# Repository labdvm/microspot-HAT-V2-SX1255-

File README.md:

# microspot-HAT-V2
SX1255 TMO microspot-HAT with integrated ceramic antennas
# V1 was deleted !

# Corrections of ceramic antenna dimensions from 16mm to 14mm.
# Added IPX connectors for external antennas.

Z32IT

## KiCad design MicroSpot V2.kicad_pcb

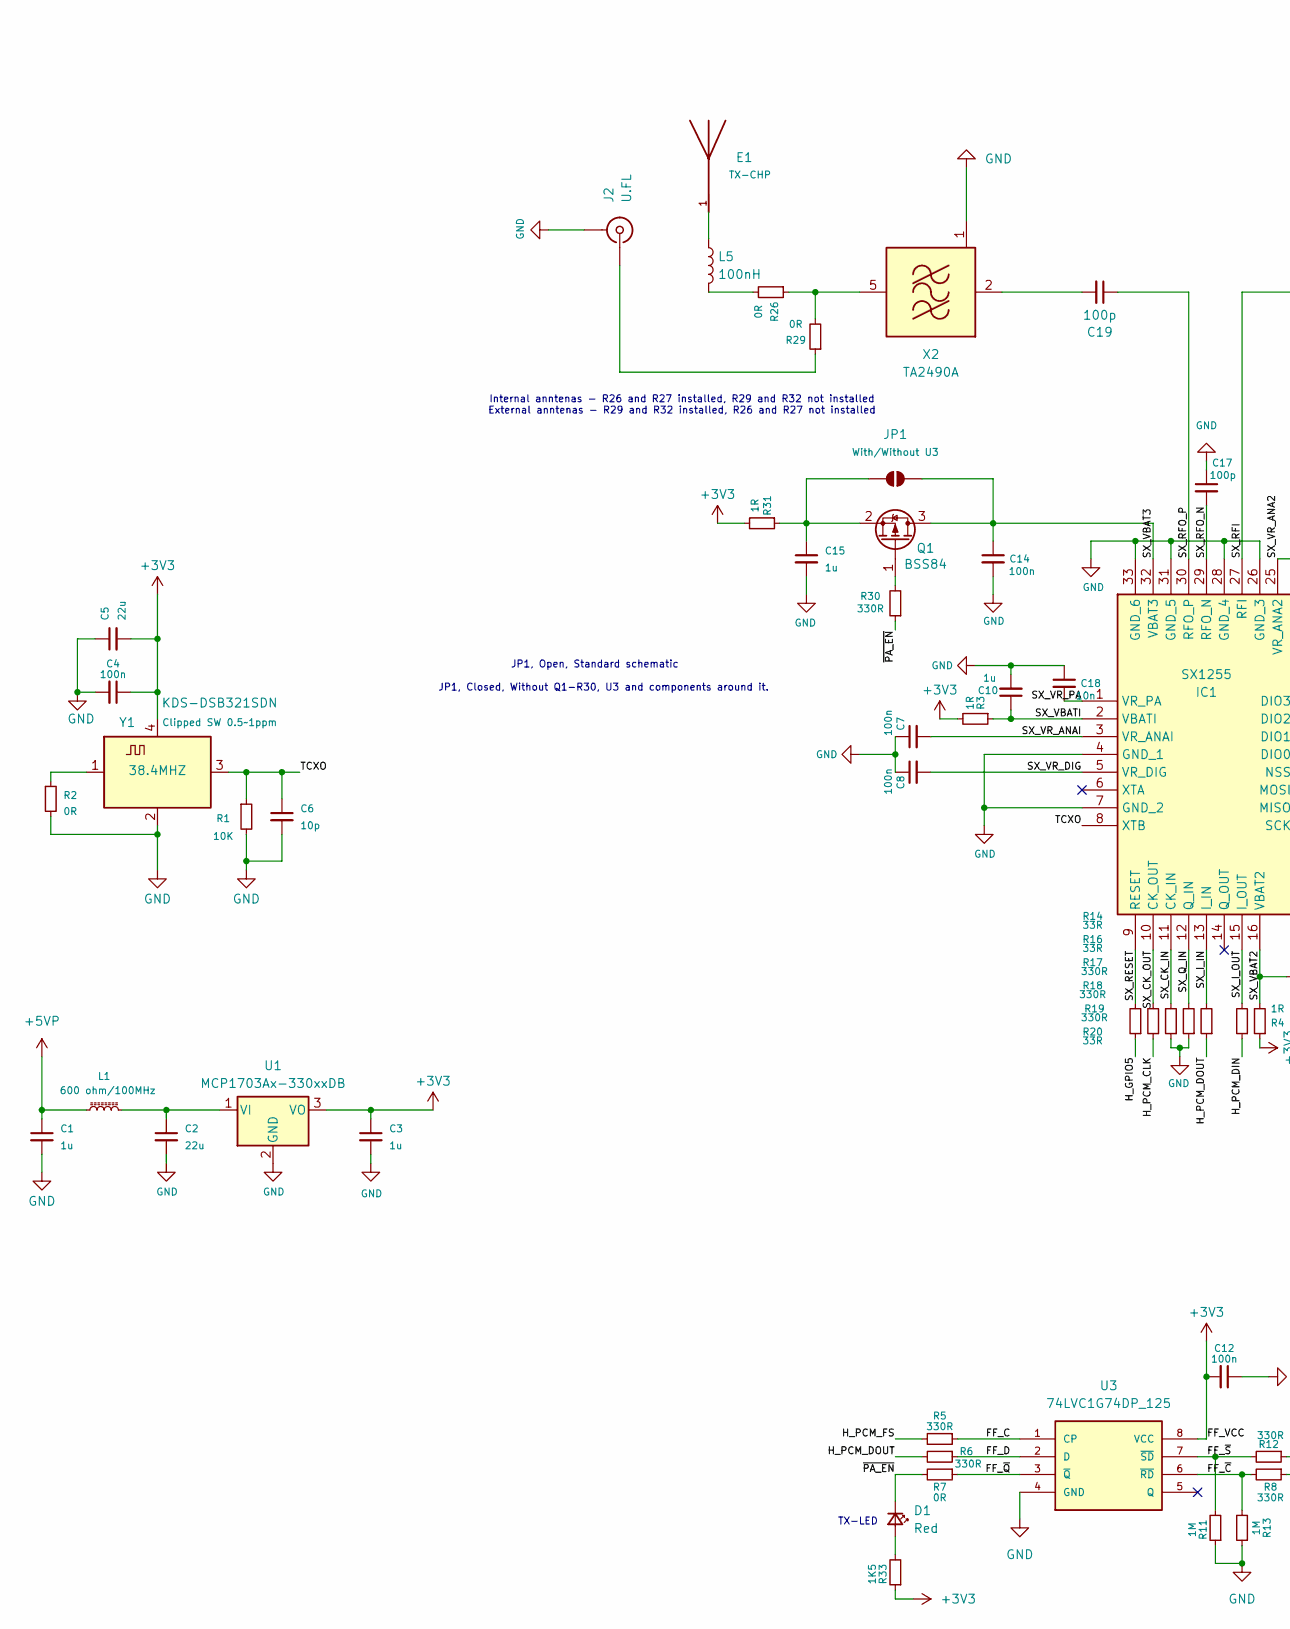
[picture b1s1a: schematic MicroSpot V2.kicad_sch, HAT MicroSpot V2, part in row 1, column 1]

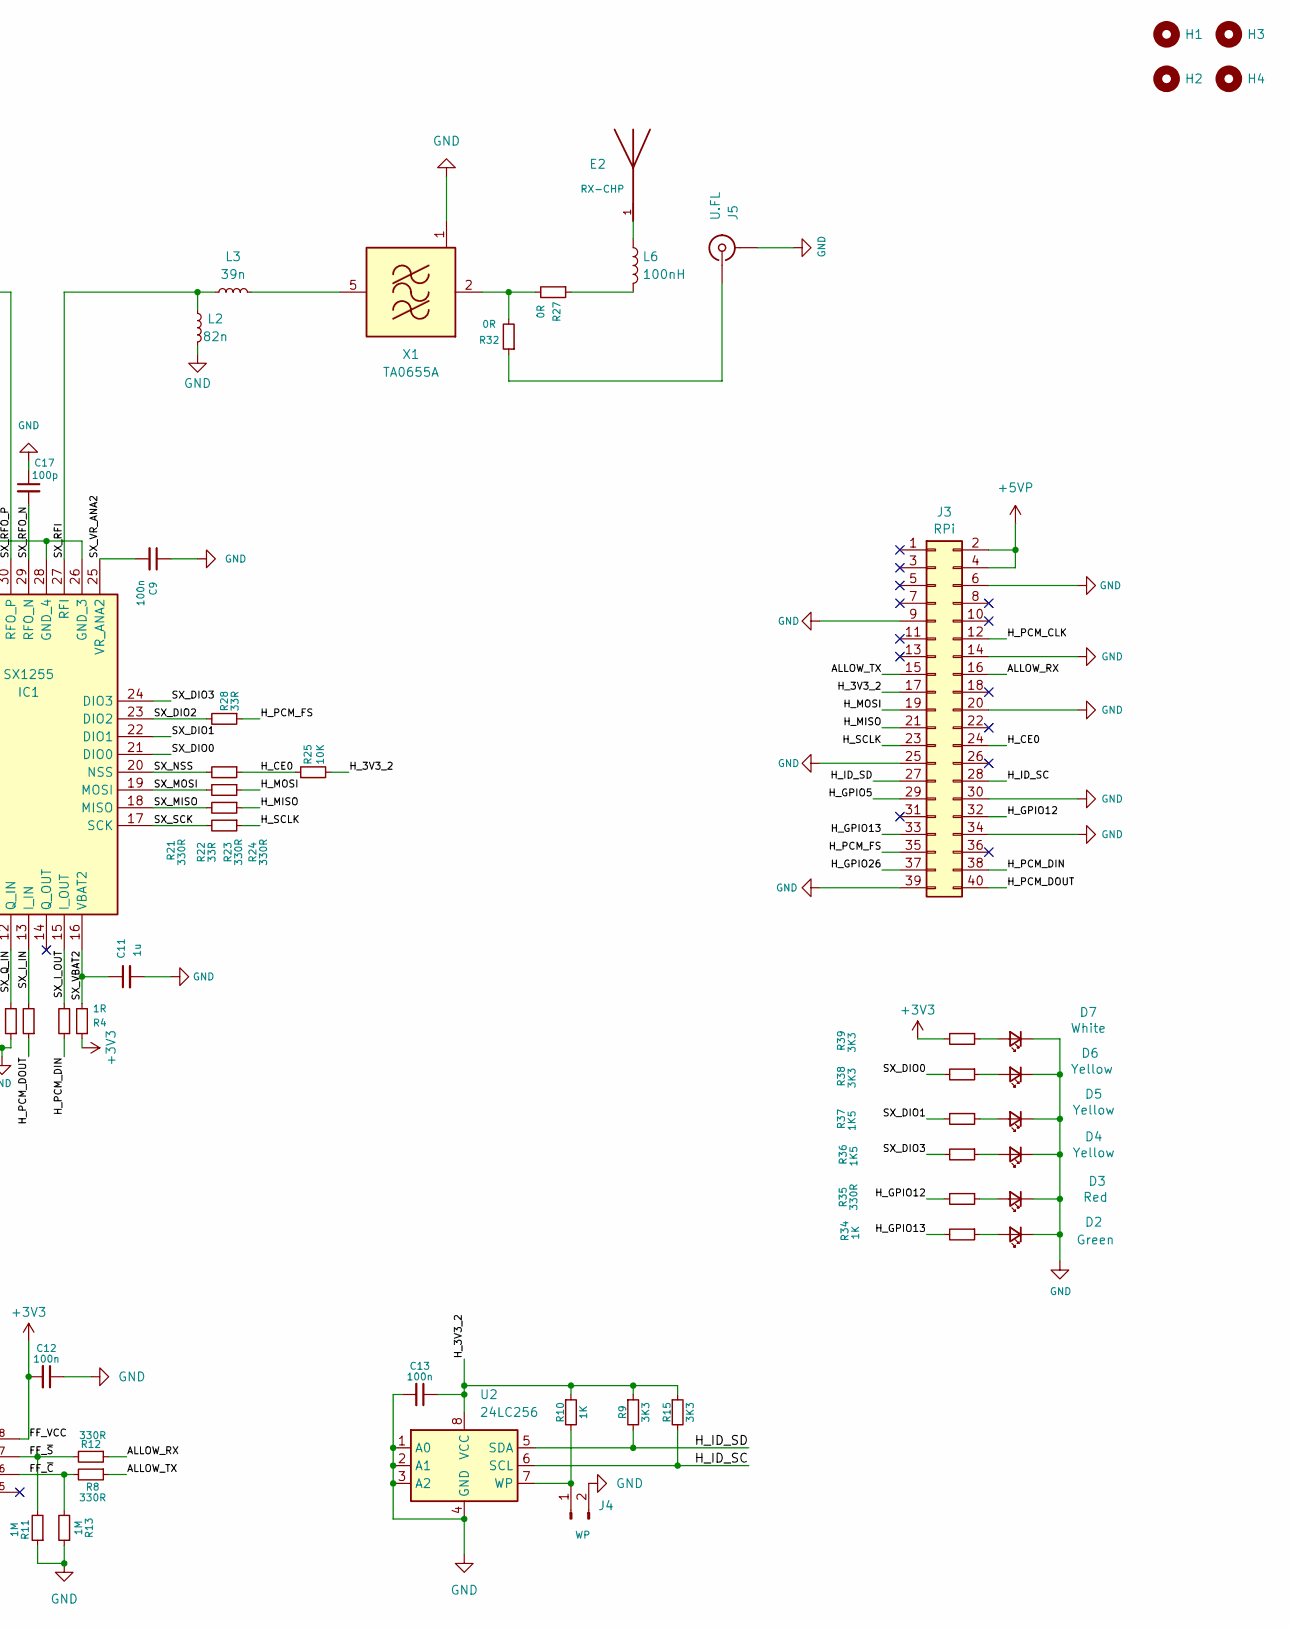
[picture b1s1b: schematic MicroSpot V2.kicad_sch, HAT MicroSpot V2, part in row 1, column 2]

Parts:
C1, C3, C10, C11, C15: 1u; C_0603_1608Metric
C2, C5: 22u; C_0805_2012Metric
C4, C7, C8, C9, C12, C13, C14: 100n; C_0603_1608Metric
C6: 10p; C_0603_1608Metric
C17, C19: 100p; C_0603_1608Metric
C18: 10n; C_0603_1608Metric
D1, D3: Red; LED_0603_1608Metric_Pad1.05x0.95mm_HandSolder
D2: Green; LED_0603_1608Metric_Pad1.05x0.95mm_HandSolder
D4, D5, D6: Yellow; LED_0603_1608Metric_Pad1.05x0.95mm_HandSolder
D7: White; LED_0603_1608Metric_Pad1.05x0.95mm_HandSolder
E1: TX-CHP; XDCR_ANT-868-CHP-T; PARTREV C
E2: RX-CHP; XDCR_ANT-868-CHP-T; PARTREV C
H1, H2, H3, H4: MountingHole; MountingHole_2.7mm_M2.5_DIN965
IC1: SX1255; QFN50P500X500X80-33N-D; MPN SX1255IWLTRT
J2, J5: U.FL; U.FL_Hirose_U.FL-R-SMT-1_Vertical; Part Number 343-CONMHF1-SMD-G-TCT-ND
J3: RPi; PinSocket_2x20_P2.54mm_Vertical
J4: WP; PinHeader_1x02_P2.54mm_Vertical
JP1: With/Without U3; SolderJumper-2_P1.3mm_Open_RoundedPad1.0x1.5mm
L1: 600 ohm/100MHz; L_0603_1608Metric
L2: 82n; L_0603_1608Metric
L3: 39n; L_0603_1608Metric
L5, L6: 100nH; L_0603_1608Metric
Q1: BSS84; SOT-23
R1, R25: 10K; R_0603_1608Metric
R2, R7, R26, R27, R29, R32: 0R; R_0603_1608Metric
R3, R4, R31: 1R; R_0603_1608Metric
R5, R6, R8, R12, R17, R18, R19, R21, R23, R24, R30, R35: 330R; R_0603_1608Metric
R9, R15, R38, R39: 3K3; R_0603_1608Metric
R10, R34: 1K; R_0603_1608Metric
R11, R13: 1M; R_0603_1608Metric
R14, R16, R20, R22, R28: 33R; R_0603_1608Metric
R33, R36, R37: 1K5; R_0603_1608Metric
U1: MCP1703Ax-330xxDB; SOT-223-3_TabPin2
U2: 24LC256; SOIC-8_3.9x4.9mm_P1.27mm
U3: 74LVC1G74DP_125; SOP65P400X110-8N; MOUSER_PART_NUMBER 771-LVC1GDP125
X1: TA0655A; Filter_SAW-6_3.8x3.8mm
X2: TA2490A; Filter_SAW_Epcos_DCC6C_3x3mm
Y1: 38.4MHZ; Crystal_SMD_3225-4Pin_3.2x2.5mm

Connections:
+3V3: C3.1, C4.1, C5.2, C12.2, R3.2, R4.1, R31.2, R33.1, R39.2, U1.3 (VO), U3.8 (VCC), Y1.4 (VDD)
+5VP: C1.1, J3.2, J3.4, L1.1
/ALLOW_RX: J3.16, R12.1
/ALLOW_TX: J3.15, R8.1
/FF_C: R5.1, U3.1 (CP)
/FF_D: R6.1, U3.2 (D)
/FF_~C: R8.2, R13.2, U3.6 (~RD)
/FF_~Q: R7.1, U3.3 (~Q)
/FF_~S: R11.2, R12.2, U3.7 (~SD)
/H_3V3_2: C13.1, J3.17, R9.1, R10.1, R15.1, R25.2, U2.8 (VCC)
/H_CE0: J3.24, R24.1, R25.1
/H_GPIO5: J3.29, R14.1
/H_GPIO12: J3.32, R35.2
/H_GPIO13: J3.33, R34.2
/H_GPIO26: J3.37
/H_ID_SC: J3.28, R15.2, U2.6 (SCL)
/H_ID_SD: J3.27, R9.2, U2.5 (SDA)
/H_MISO: J3.21, R22.1
/H_MOSI: J3.19, R23.1
/H_PCM_CLK: J3.12, R16.1
/H_PCM_DIN: J3.38, R20.1
/H_PCM_DOUT: J3.40, R6.2, R19.1
/H_PCM_FS: J3.35, R5.2, R28.1
/H_SCLK: J3.23, R21.1
/SX_CK_IN: IC1.11 (CK_IN), R17.2
/SX_CK_OUT: IC1.10 (CK_OUT), R16.2
/SX_DIO0: IC1.21 (DIO0), R38.2
/SX_DIO1: IC1.22 (DIO1), R37.2
/SX_DIO2: IC1.23 (DIO2), R28.2
/SX_DIO3: IC1.24 (DIO3), R36.2
/SX_I_IN: IC1.13 (I_IN), R19.2
/SX_I_OUT: IC1.15 (I_OUT), R20.2
/SX_MISO: IC1.18 (MISO), R22.2
/SX_MOSI: IC1.19 (MOSI), R23.2
/SX_NSS: IC1.20 (NSS), R24.2
/SX_Q_IN: IC1.12 (Q_IN), R18.2
/SX_RESET: IC1.9 (RESET), R14.2
/SX_RFI: IC1.27 (RFI), L2.2, L3.2
/SX_RFO_N: C17.2, IC1.29 (RFO_N)
/SX_RFO_P: C19.1, IC1.30 (RFO_P)
/SX_SCK: IC1.17 (SCK), R21.2
/SX_VBAT2: C11.1, IC1.16 (VBAT2), R4.2
/SX_VBAT3: C14.1, IC1.32 (VBAT3), JP1.2 (B), Q1.3 (D)
/SX_VBATI: C10.1, IC1.2 (VBATI), R3.1
/SX_VR_ANA2: C9.2, IC1.25 (VR_ANA2)
/SX_VR_ANAI: C7.2, IC1.3 (VR_ANAI)
/SX_VR_DIG: C8.2, IC1.5 (VR_DIG)
/SX_VR_PA: C18.2, IC1.1 (VR_PA)
/TCXO: C6.1, IC1.8 (XTB), R1.1, Y1.3 (OUT)
/~PA_EN: D1.1 (K), R7.2, R30.1
GND: C1.2, C2.2, C3.2, C4.2, C5.1, C6.2, C7.1, C8.1, C9.1, C10.2, C11.2, C12.1, C13.2, C14.2, C15.2, C17.1, C18.1, D2.1 (K), D3.1 (K), D4.1 (K), D5.1 (K), D6.1 (K), D7.1 (K), IC1.4 (GND_1), IC1.7 (GND_2), IC1.26 (GND_3), IC1.28 (GND_4), IC1.31 (GND_5), IC1.33 (GND_6), J2.2 (Ext), J3.6, J3.9, J3.14, J3.20, J3.25, J3.30, J3.34, J3.39, J4.2, J5.2 (Ext), L2.1, R1.2, R2.2, R11.1, R13.1, R17.1, R18.1, U1.2 (GND), U2.1 (A0), U2.2 (A1), U2.3 (A2), U2.4 (GND), U3.4 (GND), X1.1 (GND), X1.3 (GND), X1.4 (GND), X1.6 (GND), X2.1 (GND), X2.3 (GND), X2.4 (GND), X2.6 (GND), Y1.2 (GND)
unnamed: D1.2 (A), R33.2
unnamed: D2.2 (A), R34.1
unnamed: D3.2 (A), R35.1
unnamed: D4.2 (A), R36.1
unnamed: D5.2 (A), R37.1
unnamed: D6.2 (A), R38.1
unnamed: D7.2 (A), R39.1
unnamed: E1.1, L5.1
unnamed: E2.1, L6.1
unnamed: J2.1 (In), R29.1
unnamed: J4.1, R10.2, U2.7 (WP)
unnamed: J5.1 (In), R32.1
unnamed: C15.1, JP1.1 (A), Q1.2 (S), R31.1
unnamed: L5.2, R26.2
unnamed: L6.2, R27.1
unnamed: Q1.1 (G), R30.2
unnamed: C2.1, L1.2, U1.1 (VI)
unnamed: R27.2, R32.2, X1.2 (IN)
unnamed: L3.1, X1.5 (OUT)
unnamed: C19.2, X2.2 (IN)
unnamed: R26.1, R29.2, X2.5 (OUT)
unnamed: R2.1, Y1.1 (Tri-State)

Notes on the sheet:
TX-LED
JP1, Open, Standard schematic
JP1, Closed, Without Q1-R30, U3 and components around it.
Internal anntenas - R26 and R27 installed, R29 and R32 not installed External anntenas - R29 and R32 installed, R26 and R27 not installed

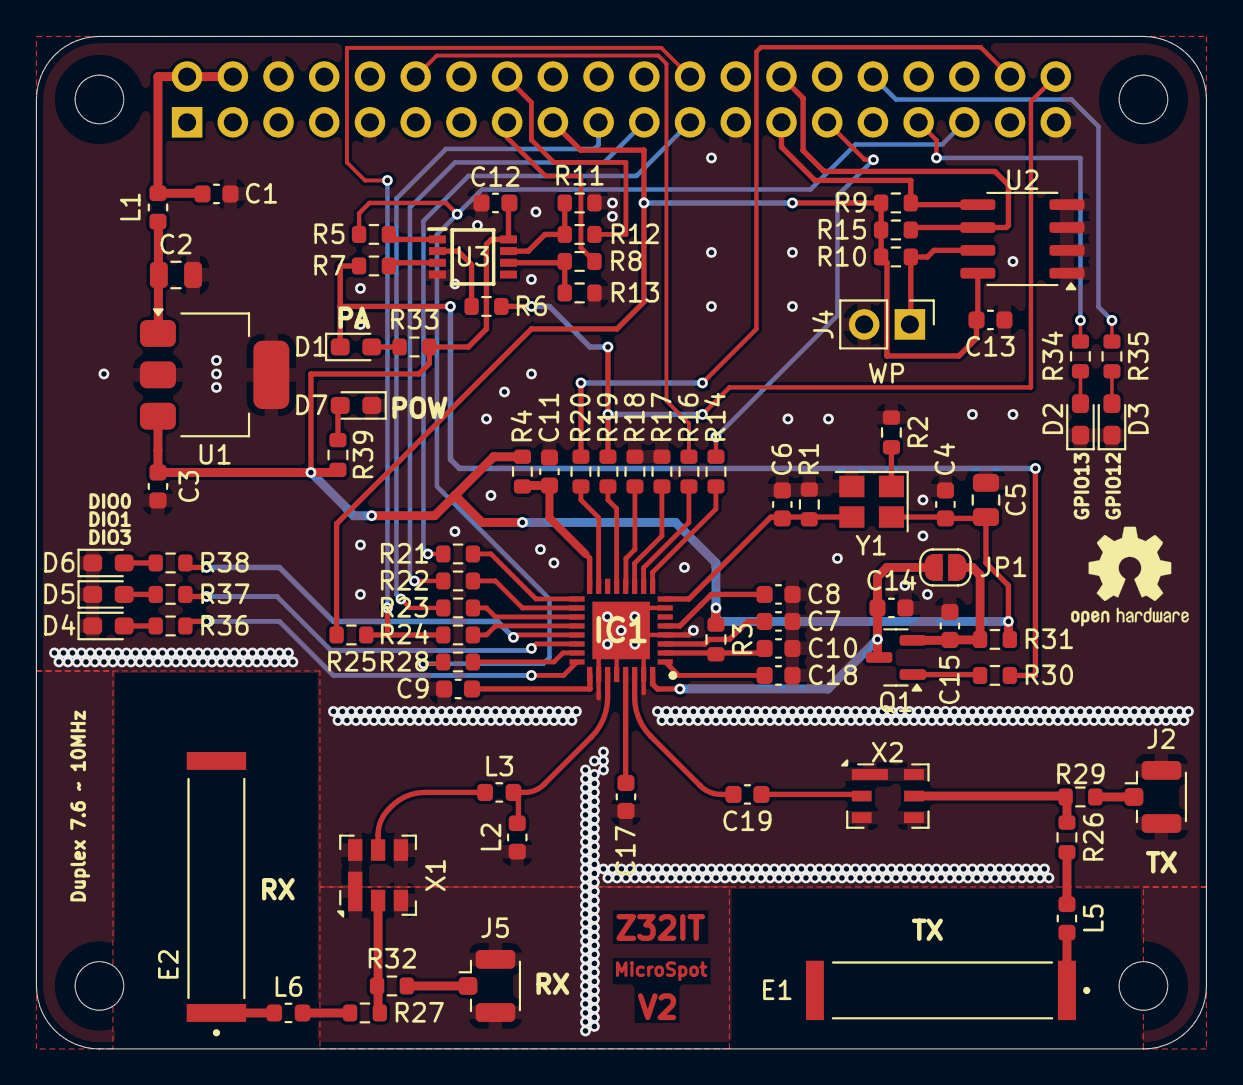
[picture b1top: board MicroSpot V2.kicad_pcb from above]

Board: 2 copper layers, 65.0 x 56.2 mm, 88 parts (1 on the bottom side), 72 nets.

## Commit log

2026-06-17 Update project name in README
2026-06-17 Update README with antenna dimension corrections and IPX connectors
2026-06-17 Update README with corrections and new features
